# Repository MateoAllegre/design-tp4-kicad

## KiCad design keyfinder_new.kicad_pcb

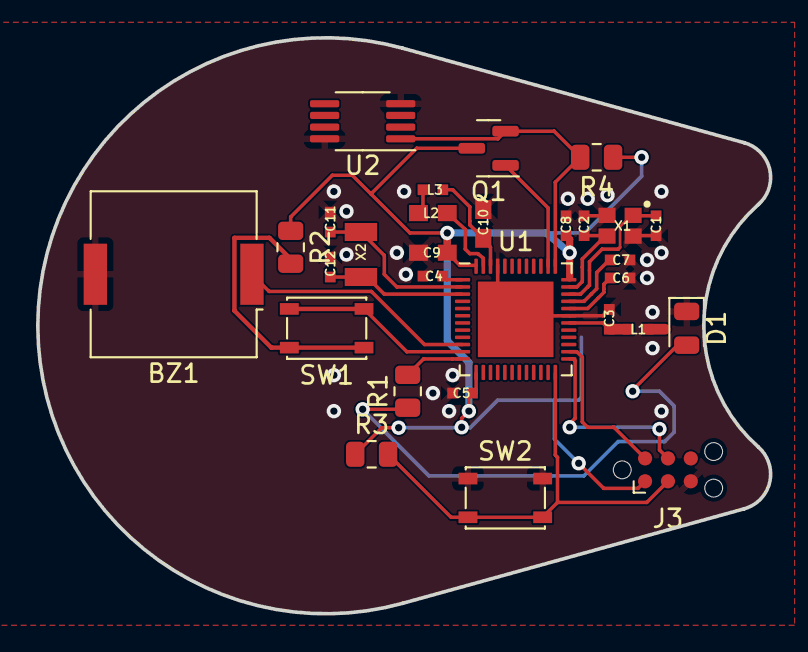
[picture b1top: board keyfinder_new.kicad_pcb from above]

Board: 2 copper layers, 40.7 x 32.0 mm, 30 parts (1 on the bottom side), 19 nets.

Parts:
BT1: Battery; BatteryHolder_Keystone_1060_1x2032
BZ1: Buzzer; Buzzer_Murata_PKMCS0909E
C1, C2, C11, C12: 12pF; RESC0402_N
C3: 0.8pF; RESC0402_N
C4, C5, C8: 100nF; RESC0402_N
C6: N.M.; RESC0402_N
C7: 100pF; RESC0402_N
C9: 4.7µF; RESC0603_N
C10: 1.0µF; RESC0603_N
D1: LED Blue; LED_0805_2012Metric
J3: Conn_ARM_SWD_TagConnect_TC2030; Tag-Connect_TC2030-IDC-NL_2x03_P1.27mm_Vertical
L1: 3.9nH; RESC0402_N
L2: 10µH; RESC0603_N
L3: 15nH; RESC0402_N
Q1: 2N7002; SOT-23
R1: 330; R_0805_2012Metric
R2, R3: 10k; R_0805_2012Metric
R4: 4.7k; R_0805_2012Metric
SW1: SW_Push; SW_SPST_PTS810
SW2: SW_Omron_B3FS; SW_SPST_PTS810
U1: NRF52832; QFN-48-1EP_6x6mm_P0.4mm_EP4.2x4.2mm
U2: DS18B20U; MSOP-8_3x3mm_P0.65mm
X1: 32MHz; BT-XTAL_2016_N
X2: 32.768kHz; XTAL_3215_N

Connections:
/P0.08: BZ1.1 (-), U1.10 (P0.08@10)
/P0.09: SW1.2, U1.11 (P0.09/NFC1@11)
/P0.10: R1.2, U1.12 (P0.10/NFC2@12)
/P0.21/RESET: J3.3 (~RESET), R3.2, SW2.2, U1.24 (P0.21/RESET@24)
/P0.25: Q1.2 (S), R4.2, U1.37 (P0.25@37), U2.1 (DQ)
/P0.26: Q1.1 (G), U1.38 (P0.26@38)
/SWDCLK: J3.4 (SWCLK), U1.25 (SWDCLK@25)
/SWDIO: J3.2 (SWDIO), U1.26 (SWDIO@26)
ANT: C3.1, L1.1
DEC4: C10.1, L3.2
GND: BT1.2 (-), BZ1.2 (+), C1.2, C2.2, C3.2, C4.2, C5.2, C6.2, C7.2, C8.2, C9.2, C10.2, C11.1, C12.1, D1.1 (K), J3.5 (GND), SW2.1, U1.31 (VSS@31), U1.45 (VSS@45), U2.4 (GND), U2.8 (V_{DD}), X1.2, X1.4
unnamed: L2.2, L3.1
unnamed: C2.1, X1.3
unnamed: D1.2 (A), R1.1
unnamed: R2.2, SW1.1
P0.00/XL1: C11.2, X2.1
P0.01/XL2: C12.2, X2.2
VCC: BT1.1 (+), C5.1, C8.1, C9.1, J3.1 (VCC), Q1.3 (D), R2.1, R3.1, R4.1, U1.13 (VDD@13), U1.36 (VDD@36), U1.48 (VDD@48)
X1: C1.1, X1.1

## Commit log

2023-11-20 Commit initial + Ajout de la resistance et de la LED
2023-11-26 Ajout de quelques composants sur le schema
2023-11-26 Ajout des composants manquants et debut du routage sur le PCB
2023-11-26 Fin du routage
2023-11-26 Correction des problemes de VCC et ajout dimensions
2023-11-26 ajout des references et liens vers DigiKey dans les composants sur le schematic
2023-11-26 Ajout du diagramme
2023-12-04 Passage sur le vrai PCB
2023-12-04 correction autosave
2023-12-10 Ajout du capteur de temperature au schema et au PCB et routage
2023-12-10 ajout du rapport et du nouveau fichier f3z
